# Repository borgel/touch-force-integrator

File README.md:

# touch-force-integrator
Microcontroller firmware which integrates touch, force sensing, and haptics logic.

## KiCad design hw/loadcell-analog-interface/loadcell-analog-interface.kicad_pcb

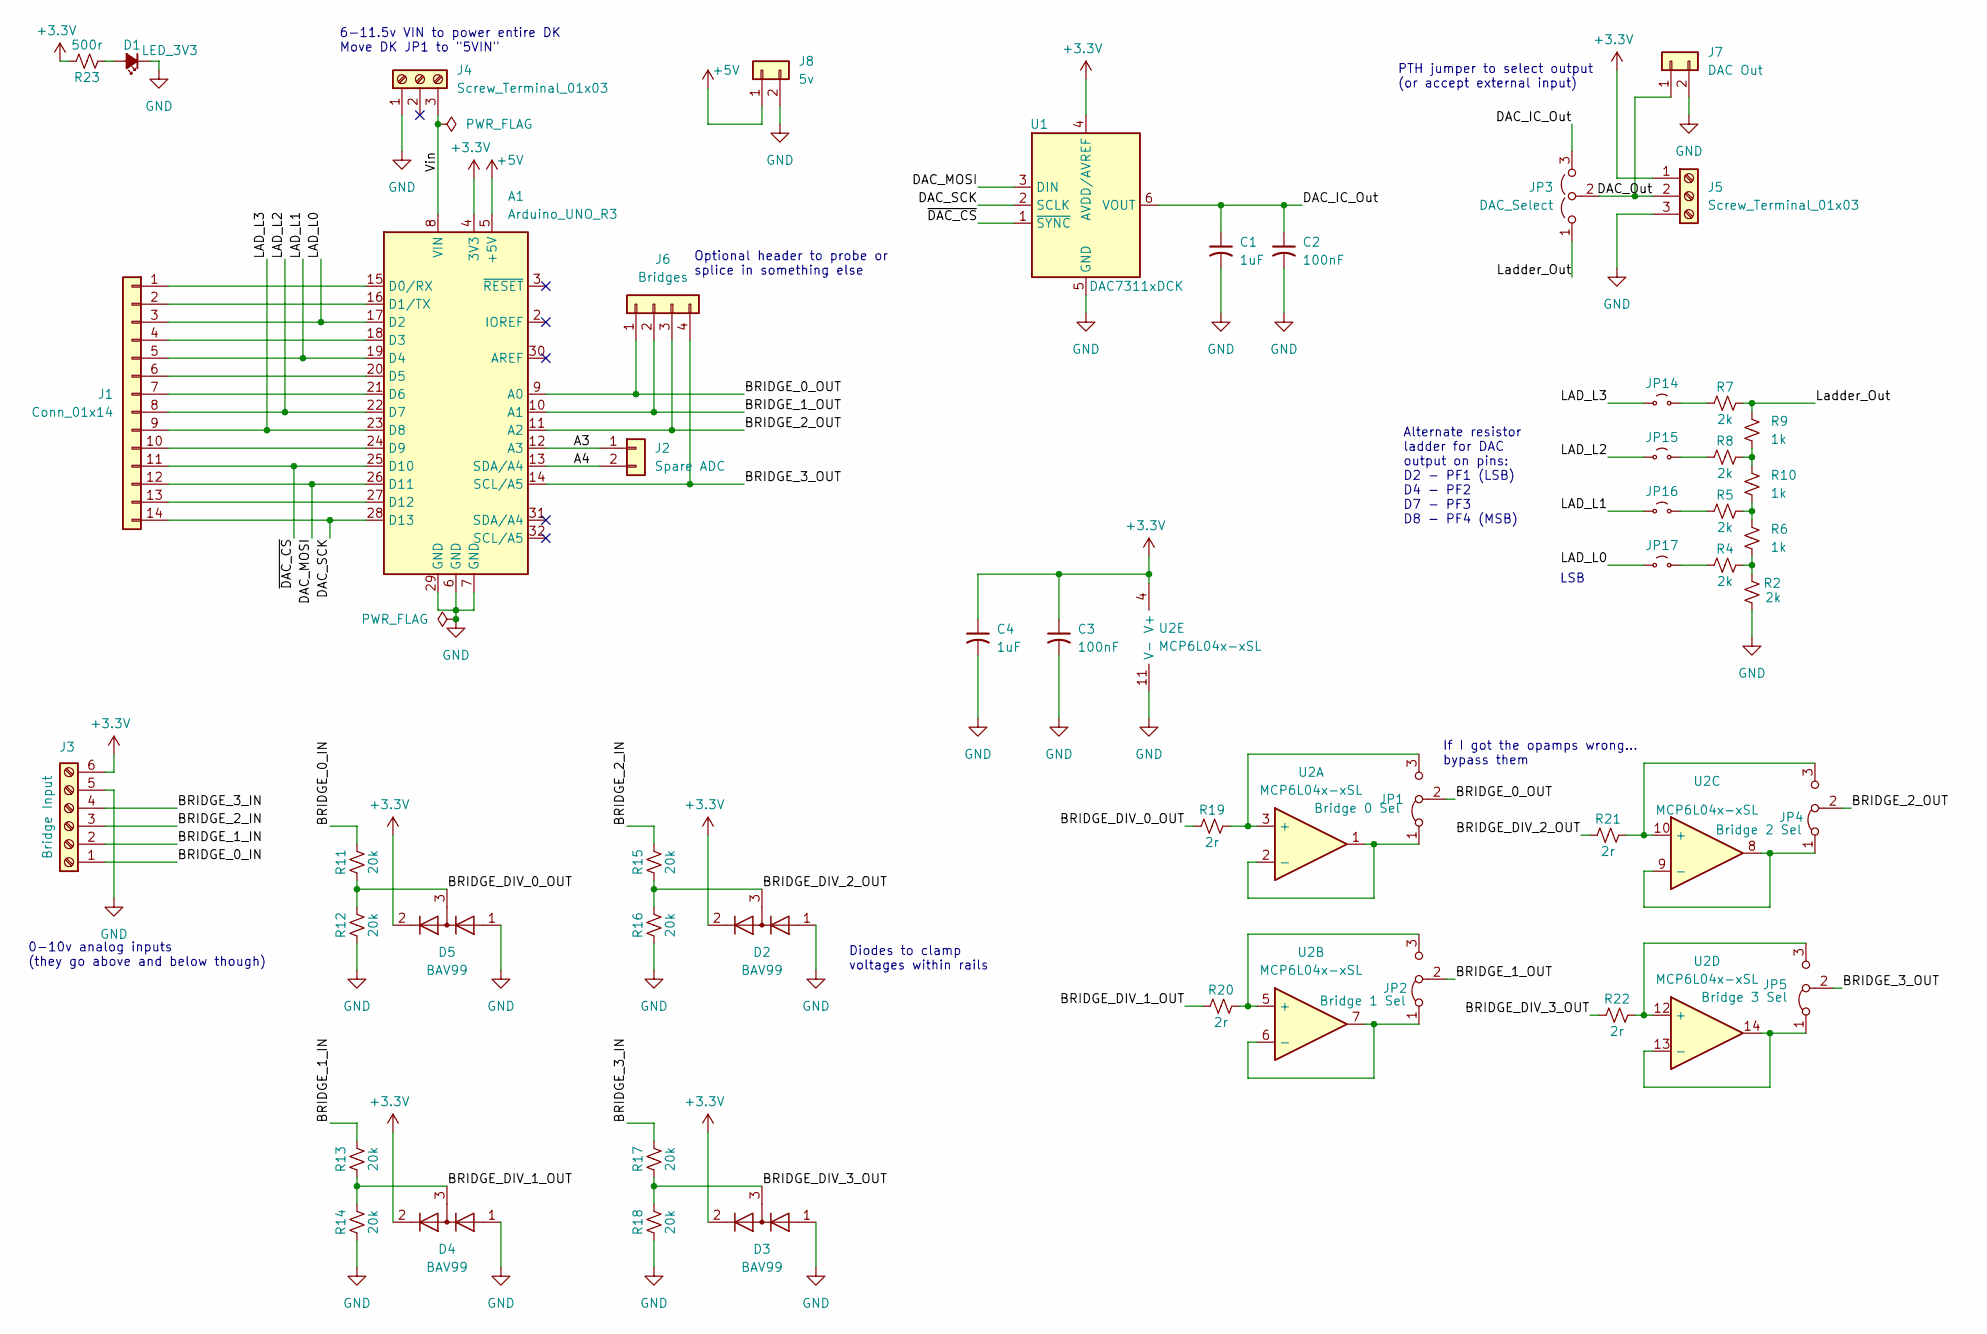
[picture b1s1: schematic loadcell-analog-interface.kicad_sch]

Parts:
A1: Arduino_UNO_R3
C1, C4: 1uF; C_0603_1608Metric
C2, C3: 100nF; C_0603_1608Metric
D1: LED_3V3; LED_0603_1608Metric
D2, D3, D4, D5: BAV99; SOT-23; LCSC C82480
J1: Conn_01x14; PinHeader_1x14_P2.54mm_Vertical
J2: Spare ADC; PinHeader_1x02_P2.54mm_Vertical
J3: Bridge Input; TerminalBlock_RND_205-00049_1x06_P5.00mm_Horizontal; LCSC C42377751
J4, J5: Screw_Terminal_01x03; TerminalBlock_RND_205-00046_1x03_P5.00mm_Horizontal; LCSC C72334
J6: Bridges; PinHeader_1x04_P2.54mm_Vertical
J7: DAC Out; PinHeader_1x02_P2.54mm_Vertical
J8: 5v; PinHeader_1x02_P2.54mm_Vertical
JP1: Bridge 0 Sel; SolderJumper-3_P1.3mm_Bridged12_RoundedPad1.0x1.5mm_NumberL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
JP2: Bridge 1 Sel; SolderJumper-3_P1.3mm_Bridged12_RoundedPad1.0x1.5mm_NumberL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
JP3: DAC_Select; PinHeader_1x03_P2.54mm_Vertical
JP4: Bridge 2 Sel; SolderJumper-3_P1.3mm_Bridged12_RoundedPad1.0x1.5mm_NumberL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
JP5: Bridge 3 Sel; SolderJumper-3_P1.3mm_Bridged12_RoundedPad1.0x1.5mm_NumberL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
JP14: LD3; SolderJumper-2_P1.3mm_Open_RoundedPad1.0x1.5mm
JP15: LD2; SolderJumper-2_P1.3mm_Open_RoundedPad1.0x1.5mm
JP16: LD1; SolderJumper-2_P1.3mm_Open_RoundedPad1.0x1.5mm
JP17: LD0; SolderJumper-2_P1.3mm_Open_RoundedPad1.0x1.5mm
R2, R4, R5, R7, R8: 2k; R_0603_1608Metric
R6, R9, R10: 1k; R_0603_1608Metric
R11, R12, R13, R14, R15, R16, R17, R18: 20k; R_0603_1608Metric
R19, R20, R21, R22: 2r; R_0603_1608Metric
R23: 500r; R_0603_1608Metric
U1: DAC7311xDCK; SOT-363_SC-70-6; LCSC C128601
U2: MCP6L04x-xSL; SOIC-14_3.9x8.7mm_P1.27mm; LCSC C626833

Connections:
+3.3V: A1.4 (3V3), C3.1, C4.1, D2.2 (A), D3.2 (A), D4.2 (A), D5.2 (A), J3.6, J5.1, R23.2, U1.4 (AVDD/AVREF), U2.4 (V+)
+5V: A1.5 (+5V), J8.1
/A3: A1.12 (A3), J2.1
/A4: A1.13 (SDA/A4), J2.2
/BRIDGE_0_IN: J3.1, R11.2
/BRIDGE_0_OUT: A1.9 (A0), J6.1, JP1.2 (C)
/BRIDGE_1_IN: J3.2, R13.2
/BRIDGE_1_OUT: A1.10 (A1), J6.2, JP2.2 (C)
/BRIDGE_2_IN: J3.3, R15.2
/BRIDGE_2_OUT: A1.11 (A2), J6.3, JP4.2 (C)
/BRIDGE_3_IN: J3.4, R17.2
/BRIDGE_3_OUT: A1.14 (SCL/A5), J6.4, JP5.2 (C)
/BRIDGE_DIV_0_OUT: D5.3 (K), R11.1, R12.2, R19.1
/BRIDGE_DIV_1_OUT: D4.3 (K), R13.1, R14.2, R20.1
/BRIDGE_DIV_2_OUT: D2.3 (K), R15.1, R16.2, R21.1
/BRIDGE_DIV_3_OUT: D3.3 (K), R17.1, R18.2, R22.1
/DAC_IC_Out: C1.1, C2.1, JP3.3 (B), U1.6 (VOUT)
/DAC_MOSI: A1.26 (D11), J1.12, U1.3 (DIN)
/DAC_Out: J5.2, J7.1, JP3.2 (C)
/DAC_SCK: A1.28 (D13), J1.14, U1.2 (SCLK)
/LAD_L0: A1.17 (D2), J1.3, JP17.1 (A)
/LAD_L1: A1.19 (D4), J1.5, JP16.1 (A)
/LAD_L2: A1.22 (D7), J1.8, JP15.1 (A)
/LAD_L3: A1.23 (D8), J1.9, JP14.1 (A)
/Ladder_Out: JP3.1 (A), R7.2, R9.2
/Vin: A1.8 (VIN), J4.3
/~DAC_CS: A1.25 (D10), J1.11, U1.1 (~SYNC)
GND: A1.6 (GND), A1.7 (GND), A1.29 (GND), C1.2, C2.2, C3.2, C4.2, D1.1 (K), D2.1 (K), D3.1 (K), D4.1 (K), D5.1 (K), J3.5, J4.1, J5.3, J7.2, J8.2, R2.2, R12.1, R14.1, R16.1, R18.1, U1.5 (GND), U2.11 (V-)
unnamed: A1.15 (D0/RX), J1.1
unnamed: A1.16 (D1/TX), J1.2
unnamed: A1.18 (D3), J1.4
unnamed: A1.20 (D5), J1.6
unnamed: A1.21 (D6), J1.7
unnamed: A1.24 (D9), J1.10
unnamed: A1.27 (D12), J1.13
unnamed: D1.2 (A), R23.1
unnamed: JP1.1 (A), U2.1, U2.2 (-)
unnamed: JP1.3 (B), R19.2, U2.3 (+)
unnamed: JP2.1 (A), U2.6 (-), U2.7
unnamed: JP2.3 (B), R20.2, U2.5 (+)
unnamed: JP4.1 (A), U2.8, U2.9 (-)
unnamed: JP4.3 (B), R21.2, U2.10 (+)
unnamed: JP5.1 (A), U2.13 (-), U2.14
unnamed: JP5.3 (B), R22.2, U2.12 (+)
unnamed: JP14.2 (B), R7.1
unnamed: JP15.2 (B), R8.1
unnamed: JP16.2 (B), R5.1
unnamed: JP17.2 (B), R4.1
unnamed: R2.1, R4.2, R6.1
unnamed: R5.2, R6.2, R10.1
unnamed: R8.2, R9.1, R10.2

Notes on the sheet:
PTH jumper to select output (or accept external input)
LSB
6-11.5v VIN to power entire DK Move DK JP1 to "5VIN"
Alternate resistor ladder for DAC output on pins: D2 - PF1 (LSB) D4 - PF2 D7 - PF3 D8 - PF4 (MSB)
0-10v analog inputs (they go above and below though)
Diodes to clamp voltages within rails
If I got the opamps wrong... bypass them
Optional header to probe or splice in something else

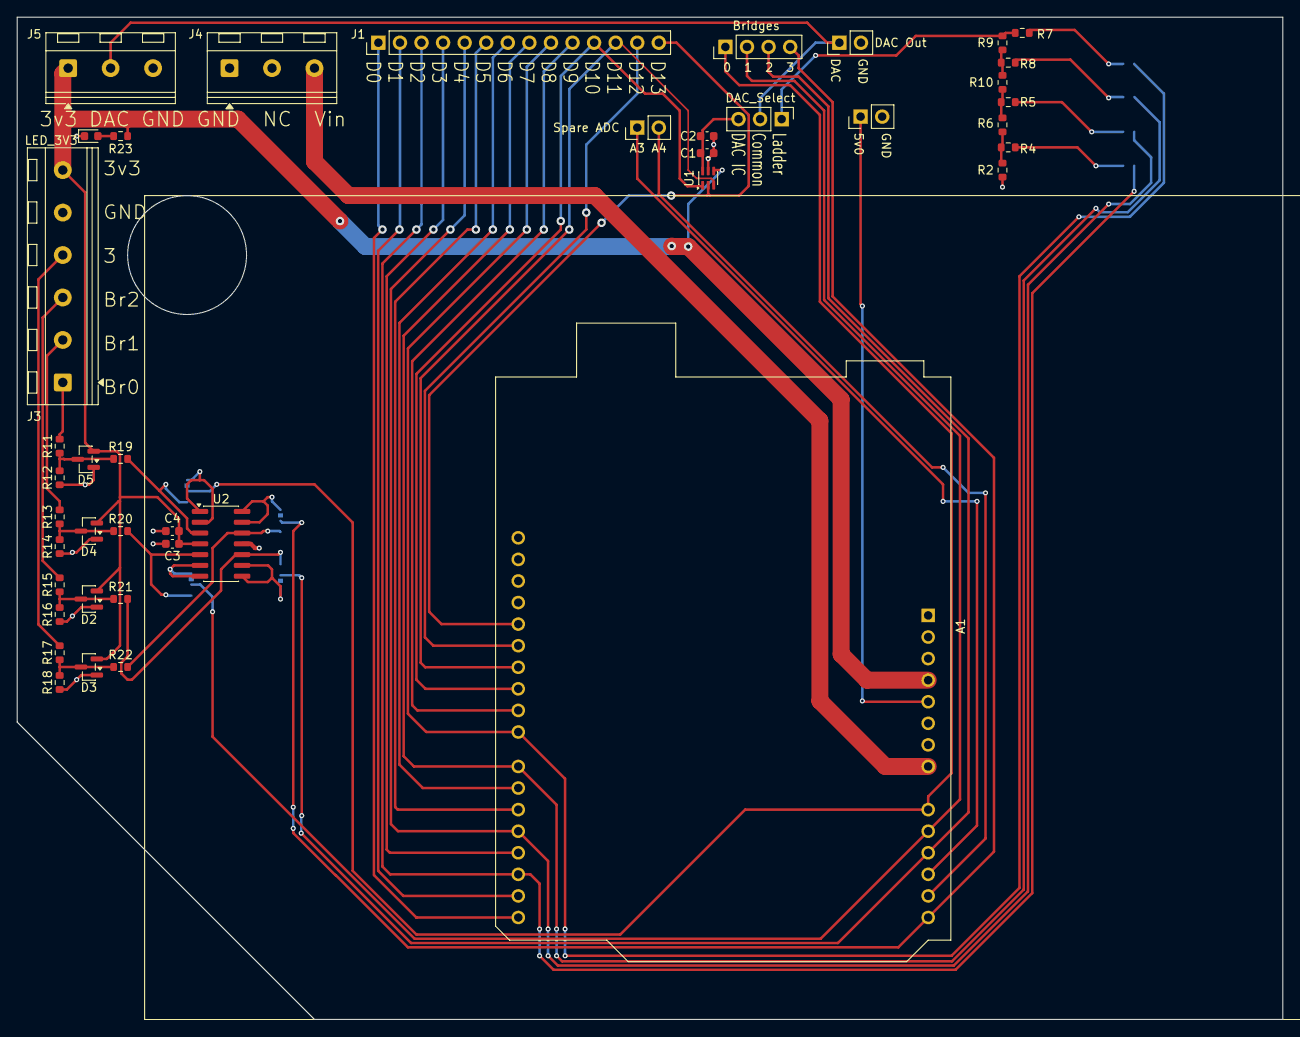
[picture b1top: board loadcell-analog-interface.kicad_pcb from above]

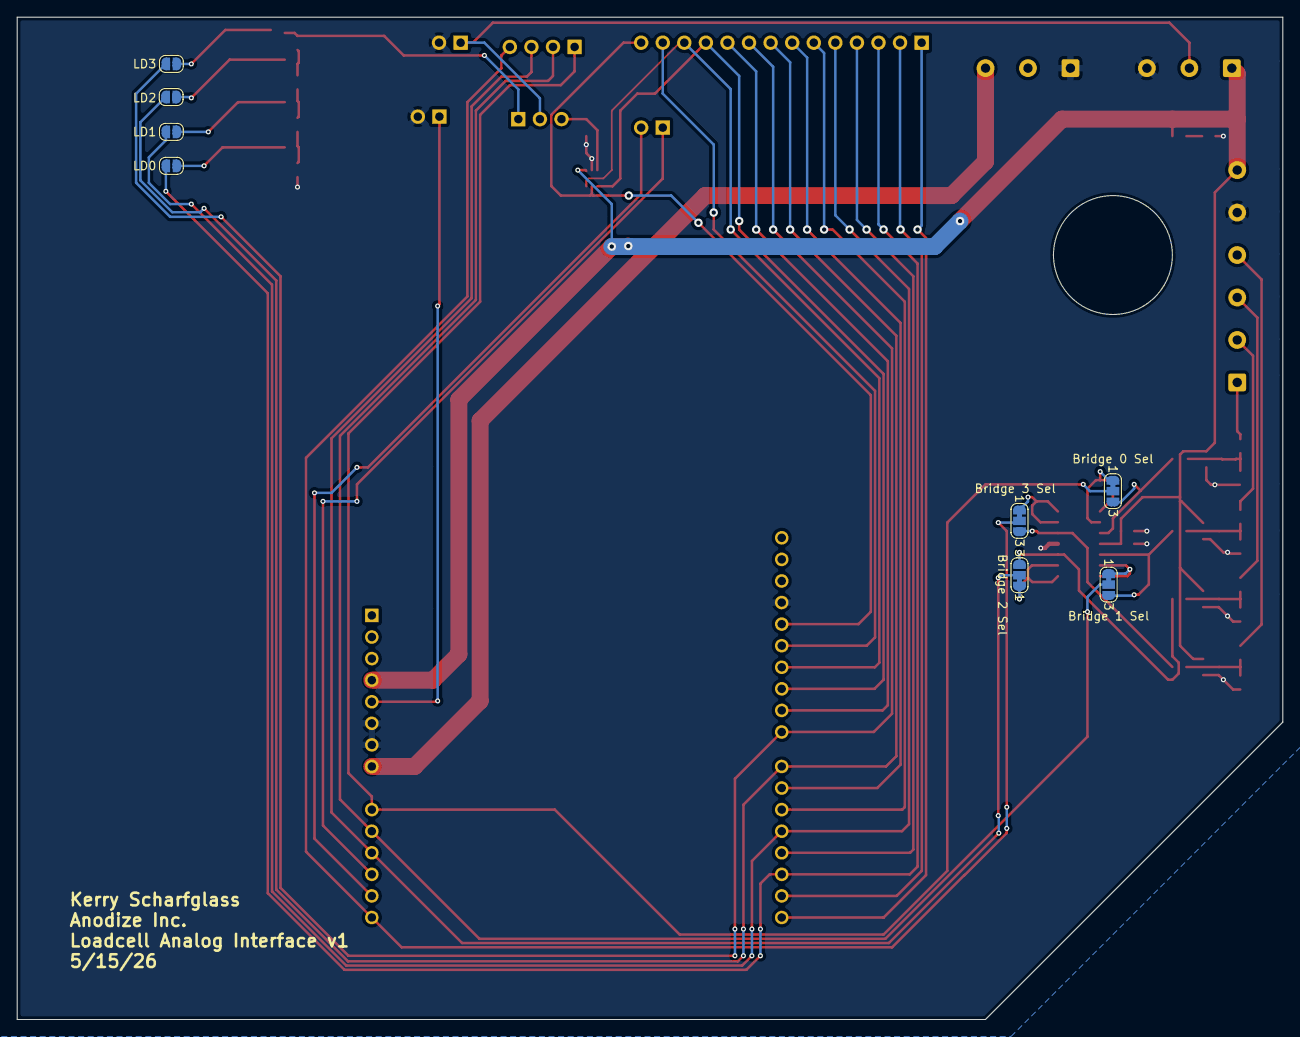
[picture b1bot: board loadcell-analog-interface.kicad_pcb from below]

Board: 2 copper layers, 149.0 x 118.0 mm, 50 parts (8 on the bottom side), 51 nets.

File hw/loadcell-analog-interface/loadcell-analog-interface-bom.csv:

"Reference","Value","Footprint","LCSC"
"C1,C4","1uF","Capacitor_SMD:C_0603_1608Metric",""
"C2,C3","100nF","Capacitor_SMD:C_0603_1608Metric",""
"D1","LED_3V3","LED_SMD:LED_0603_1608Metric",""
"D2,D3,D4,D5","BAV99","Package_TO_SOT_SMD:SOT-23","C82480"
"J3","Bridge Input","TerminalBlock_RND:TerminalBlock_RND_205-00049_1x06_P5.00mm_Horizontal","C42377751"
"J4,J5","Screw_Terminal_01x03","TerminalBlock_RND:TerminalBlock_RND_205-00046_1x03_P5.00mm_Horizontal","C72334"
"R2,R4,R5,R7,R8","2k","Resistor_SMD:R_0603_1608Metric",""
"R6,R9,R10","1k","Resistor_SMD:R_0603_1608Metric",""
"R11,R12,R13,R14,R15,R16,R17,R18","20k","Resistor_SMD:R_0603_1608Metric",""
"R19,R20,R21,R22","2r","Resistor_SMD:R_0603_1608Metric",""
"R23","500r","Resistor_SMD:R_0603_1608Metric",""
"U1","DAC7311xDCK","Package_TO_SOT_SMD:SOT-363_SC-70-6","C128601"
"U2","MCP6L04x-xSL","Package_SO:SOIC-14_3.9x8.7mm_P1.27mm","C626833"

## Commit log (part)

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2026-04-24 Add an ST example of USB host
2026-04-24 Begin adding touchscreen support
2026-04-24 Fix wide array of bugs in ST's HID parsing
    The stock HID_ReadItem and HID_WriteItem in ST's USB Host middleware
    silently produce wrong results for any HID field wider than one byte,
    and most array writes silently fail. Symptoms on the multi-touch
    digitizer show up as stuck-looking X/Y coordinates, a scan time that
    only ever takes values that are multiples of 2^24, and vendor output
    reports where only byte 0 ever changes.
2026-04-24 Correct reassembly of full Report 1 frames
2026-04-24 We're unpacking USB messages!
2026-04-24 Start writing our own Wisecoco class
2026-04-24 Calling into my code now and not faulting, next step get reports
2026-04-24 Our init added, debugging hardfault
2026-04-24 Update generated HID report macros to correct size errors
2026-04-24 Receive and reassemble entire Report 1 frames
2026-04-24 Fix memory safety issue in vendor code
2026-04-24 Fully decode fingers!
2026-04-24 Wisecoco gets through filtering and calls init function (not wired yet)
2026-04-24 Add an example driving the STM32H7S78-DK LCD
2026-04-24 Add Boot_XIP.hex for the devkit
    Sourced from ST's examples here:
    https://github.com/STMicroelectronics/STM32CubeH7RS/tree/main/Projects/STM32H7S78-DK/Templates/Template_XIP
2026-04-24 Add LCD example launch config
2026-04-27 Make a cube bounce around the screen
2026-04-27 Broken attempts to adapt the 2DDMA example to use the DK BSP example
2026-04-27 Start getting the HID example compiling with the full BSP demo drivers
2026-04-28 Ugly WIP got screen to turn on in HID demo
2026-04-28 Undo bootloader modifications and switch example code to use HSE for PLL3
2026-04-28 Fix DMA2D example
2026-04-28 Get USB example back to white screen with DMA2D example components
2026-04-28 Fix PLL3 config to get the DMA2D code working in the HID demo
2026-04-28 WIP re-enable BSP LCD functions with new PLL config
2026-04-28 Apply a set of fixes to get display completely working
2026-04-29 Add higher level LCD primitives and switch to them
2026-04-29 Remove DMA2D test code cruft
2026-04-29 Basic visualization of touches on the LCD
2026-04-29 Add double buffering to _discover_lcd driver
2026-04-29 Integrate double buffering in finger position rendering
2026-04-29 Only show touches that are touching down
2026-04-30 Copy HID_RTOS to refactor into main project
2026-04-30 Modify copied project to add USB Device code
2026-05-05 Device boots and device mode CDC works, but host broken
2026-05-05 Remove project config files for tools we don't use
2026-05-05 Clock config fixes from Claude (still not working)
2026-05-05 Host and CDC work!
    Claude observed that USB2 CANNOT provide VBus to a USB device and so is sink-only. This change
    is Claude swapping the host/device USB ports, which got everything working!
2026-05-05 Remove unused file and USE_USBD_HS macro
2026-05-05 Claude-generated example of USB CDC for serial comms
2026-05-05 Add a function to rotate the representation of touch coordinates
2026-05-05 Rotate the LCD touch preview to match the physical screen
2026-05-05 Split up LCD drawing across multiple layers to reduce redraws
2026-05-05 Split USB handling and LCD drawing into two tasks
    Add concurrency protection to the Wisecoco driver
2026-05-06 Add nanopb as a submodule
2026-05-06 Add nanopb to firmware build
2026-05-08 Enable HAL RNG
2026-05-08 fixup! Enable HSI48 in HapticArea_Init so RNG actually clocks
2026-05-08 Ignore certain examples
2026-05-09 Update label for areas
2026-05-16 Complete v1 analog interface board
    Sent out to fab at JLCPCB just now.
